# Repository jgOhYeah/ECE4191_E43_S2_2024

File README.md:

# ECE4191_E43_S2_2024
Project repository for ECE4191, Group 43, Semester 2, 2024

The main code is in [`main_software`](./main_software/). An MQTT broker on localhost is assumed, edit `MQTT_HOST` in [`defines.py`](./main_software/defines.py) to set otherwise.

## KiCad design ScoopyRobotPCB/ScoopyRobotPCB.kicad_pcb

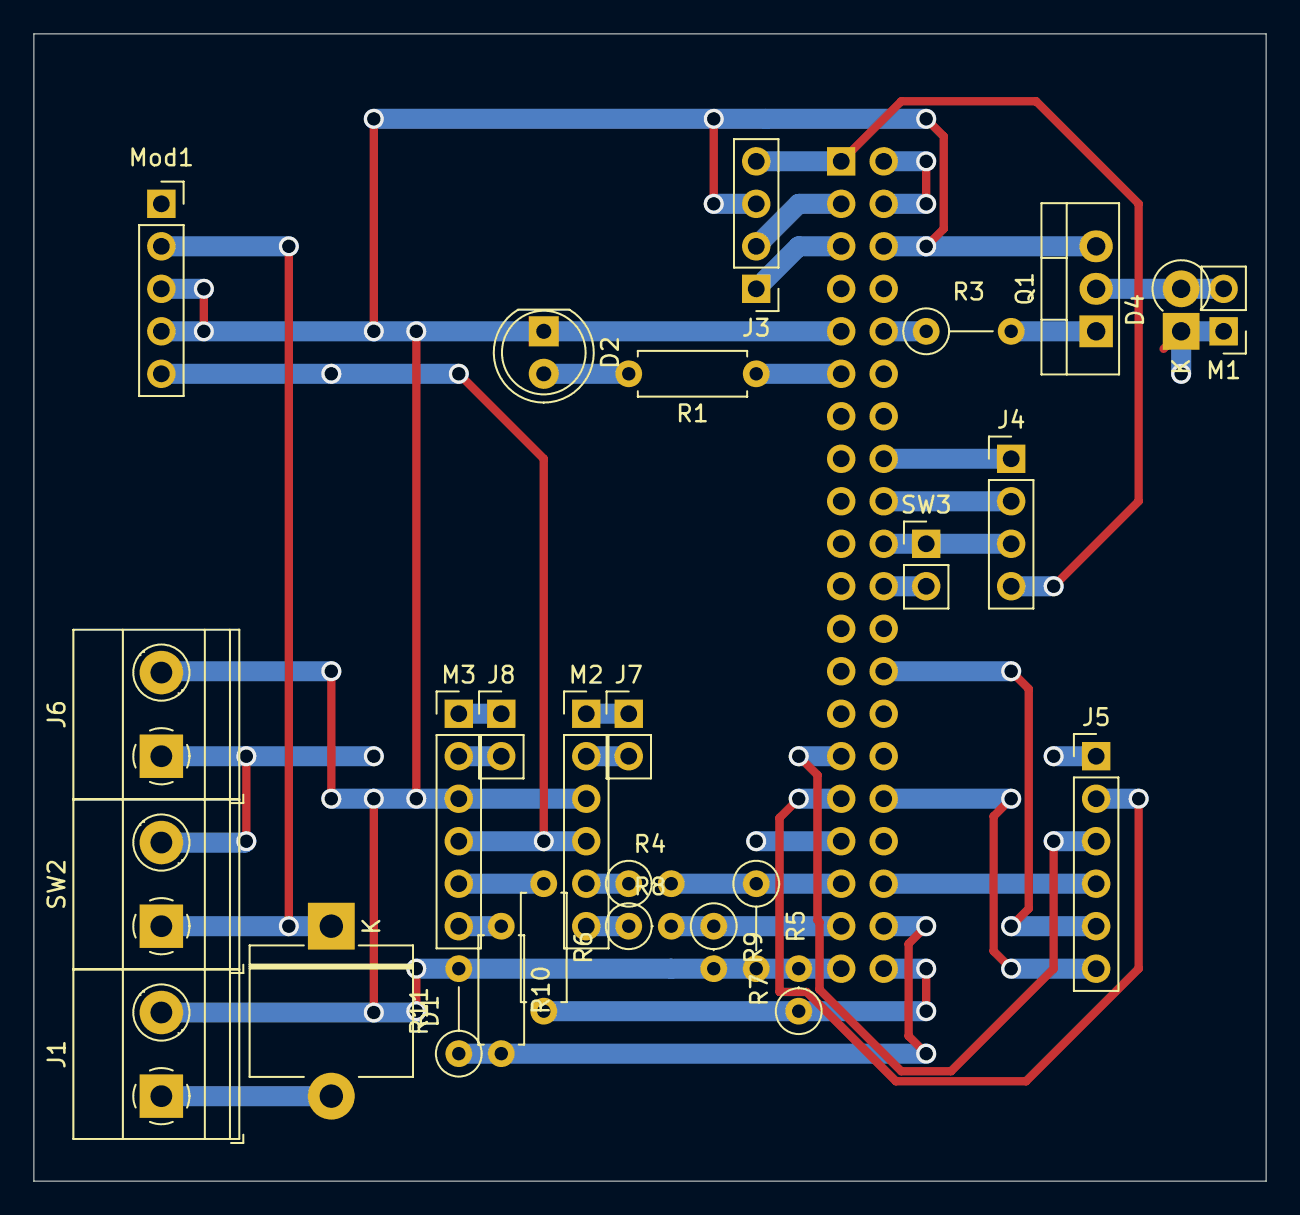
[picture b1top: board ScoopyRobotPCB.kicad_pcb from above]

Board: 4 copper layers, 73.7 x 68.6 mm, 28 parts (1 on the bottom side), 34 nets.

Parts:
D1: 6A Rectifier diode; D_5KP_P10.16mm_Horizontal
D2: LED; LED_D5.0mm
D4: 1N4004; D_DO-41_SOD81_P2.54mm_Vertical_KathodeUp
J1: 18V battery; TerminalBlock_Phoenix_MKDS-1,5-2_1x02_P5.00mm_Horizontal
J2: Raspberry_Pi_Header; PinSocket_2x20_P2.54mm_Vertical
J3: Left colour sensor; PinHeader_1x04_P2.54mm_Vertical
J4: Right colour sensor; PinHeader_1x04_P2.54mm_Vertical
J5: Wheels; PinHeader_1x06_P2.54mm_Vertical
J6: Power; TerminalBlock_Phoenix_MKDS-1,5-2_1x02_P5.00mm_Horizontal
J7: Left; PinHeader_1x02_P2.54mm_Vertical
J8: Right; PinHeader_1x02_P2.54mm_Vertical
M1: Chain gearmotor; PinHeader_1x02_P2.54mm_Vertical
M2: Left motor; PinHeader_1x06_P2.54mm_Vertical
M3: Right motor; PinHeader_1x06_P2.54mm_Vertical
Mod1: D24V25F5 voltage regulator module; PinSocket_1x05_P2.54mm_Vertical
Q1: 2SD1308; TO-220-3_Vertical
R1: 150; R_Axial_DIN0207_L6.3mm_D2.5mm_P7.62mm_Horizontal
R3: 390; R_Axial_DIN0207_L6.3mm_D2.5mm_P5.08mm_Vertical
R4, R7, R8, R9: 10k; R_Axial_DIN0207_L6.3mm_D2.5mm_P2.54mm_Vertical
R5, R11: 10k; R_Axial_DIN0207_L6.3mm_D2.5mm_P5.08mm_Vertical
R6, R10: 10k; R_Axial_DIN0207_L6.3mm_D2.5mm_P7.62mm_Horizontal
SW2: Emergency stop; TerminalBlock_Phoenix_MKDS-1,5-2_1x02_P5.00mm_Horizontal
SW3: Roller position; PinHeader_1x02_P2.54mm_Vertical

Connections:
+3.3V: J2.1 (3V3), J3.4, J4.4
+5V: J2.2 (5V), J2.4 (5V), M2.4 (Enc_VCC), M3.4 (Enc_VCC), Mod1.5 (OUT)
+BATT: D1.1 (K), Mod1.2 (VIN), SW2.1 (A)
/Chain motor: J2.10 (RXD/GPIO15), R3.1
/Chain position: J2.22 (GPIO25), SW3.2 (B)
/L.En: J2.33 (GPIO13/PWM1), J5.1
/L.Enc_A: J2.35 (GPIO19/MISO1), R4.2, R5.1
/L.Enc_B: J2.37 (GPIO26), R8.2, R9.1
/L.Mot_A: J2.29 (GPIO05/GCLK1), J5.3
/L.Mot_B: J2.31 (GPIO06/GCLK2), J5.2
/LC.SCL: J2.3 (GPIO02/SDA), J3.2
/LC.SDA: J2.5 (GPIO03/SCL), J3.1
/LMA: J7.1, M2.1 (Motor)
/LMB: J7.2, M2.2 (Motor)
/R.En: J2.32 (PWM0/GPIO12), J5.6
/R.Enc_A: J2.38 (MOSI1/GPIO20), R10.2, R11.1
/R.Enc_B: J2.40 (SCLK1/GPIO21), R6.2, R7.1
/R.Mot_A: J2.26 (CE1/GPIO07), J5.5
/R.Mot_B: J2.36 (GPIO16), J5.4
/RC.SCL: J2.18 (GPIO24), J4.2
/RC.SDA: J2.16 (GPIO23), J4.1
/RMA: J8.1, M3.1 (Motor)
/RMB: J8.2, M3.2 (Motor)
/UI.LED0: J2.11 (GPIO17), R1.1
GND: D2.1 (K), J1.2, J2.6 (Ground), J2.9 (Ground), J2.14 (Ground), J2.20 (Ground), J2.25 (Ground), J2.30 (Ground), J2.34 (Ground), J2.39 (Ground), J3.3, J4.3, J6.2, M2.3 (Enc_GND), M3.3 (Enc_GND), Mod1.3 (GND), Mod1.4 (GND), Q1.3 (E), R5.2, R7.2, R9.2, R11.2, SW3.1 (A)
unnamed: D1.2 (A), J1.1
unnamed: D2.2 (A), R1.2
unnamed: D4.2 (A), M1.2 (-), Q1.2 (C)
unnamed: M2.5 (Enc_A), R4.1
unnamed: M2.6 (Enc_B), R8.1
unnamed: M3.5 (Enc_A), R6.1
unnamed: M3.6 (Enc_B), R10.1
unnamed: Q1.1 (B), R3.2
Vdrive: D4.1 (K), J6.1, M1.1 (+), SW2.2 (B)

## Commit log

2024-08-01 rough cad on the tray
2024-08-01 Drives motors forwards and backwards.
2024-08-05 tube and baseplate for proposal
2024-08-05 modified baseplate cad
2024-08-06 added cad for given models
2024-08-11 Started schematic for robot
2024-08-11 Fixed typos in labels, connected properly now
2024-08-11 Fixing mistakes and typos in schematic, assigning footprints, starting veroboard layout
2024-08-14 Added voltage dividers for encoder, need to update layout to make way for ethernet header
2024-08-15 odometry file
2024-08-15 custom cad for demo 1
2024-08-15 downloaded cad
2024-08-15 Adding CV Jupyter file
2024-08-15 edits
2024-08-15 Motors drive with enable pins as per schematic
2024-08-15 encoder validation print statements
2024-08-15 Checked pins on odometry
2024-08-15 Added missing track on PCB
2024-08-15 Odemetry using rotary encoder object.
2024-08-20 starting to work on development for ppretrained model
2024-08-20 removing unnecessary files
2024-08-20 restoring envirnment files from raspberry pi
2024-08-22 changes to Pretrained model code, getting it ready for training
2024-08-22 time loop to check encoder
2024-08-22 Added software structure
2024-08-22 changes to gitgnore
2024-08-22 adding to odometry.py
2024-08-22 edit MQTTTopics.ODOMETRY_GO_HOME
2024-08-22 Added basic logic to control
2024-08-23 Adding saved mobileNET model
2024-08-24 object detection model in action
2024-08-24 added different models
2024-08-26 added NMS and Conditions to get rid of false positives
2024-08-26 added distance code within detect_v2
2024-08-26 Cleaning up CV folder and adding comments and acknowledgments for main codebases.
2024-08-26 moving archive folder into CV
2024-08-27 mqtt edits
2024-08-27 change update odometry
2024-08-27 edit drive_to_steps
2024-08-27 print
2024-08-27 change
2024-08-27 motor control thread
2024-08-27 Added normalisation function into detect_v2
2024-08-27 modifying detect_v2
2024-08-27 Basic position and heading odometry works
2024-08-27 Goes home, side broken into a parent class ready for PI control
2024-08-28 Attempt at writing a direct return to home
2024-08-28 Testing return to origin with turtle, moving directly
2024-08-28 Startup script written, renamed "rotations" to "distance" in odometry, direct return to origin works
2024-08-28 Mostly drives to ball
2024-08-28 Contact and go home works in control
2024-08-28 Return to home is completed in small steps.
2024-08-28 Sends status messages, rotation angle corrected
2024-08-29 Milestone 1 config, moves backwards after touching.
2024-08-31 added CV/images/ and CV/saved_models/checkpoitns to git ignore as they are too large
2024-09-04 Untested position and speed controller written
2024-09-04 Gets the speed, calculates the heading, velocity and rotation center.
2024-09-04 Predicts position for the vehicle.
2024-09-07 pushing code from the pi
2024-09-09 Added code for taking training images, and some dependencies in comp_vis environment
2024-09-11 adding pretrained mobilenet model on new dataset
2024-09-11 started working training code for YOLO model
2024-09-11 PI values seem somewhat ok
2024-09-12 Started implementing acceleration controller (broken).
2024-09-15 changes to YOLO Training
2024-09-15 updates on YOLO_training
2024-09-15 YOLO model called via ultralytics in detect file
2024-09-15 Implementing acceleration control and logging
2024-09-15 Acceleration and speed control params are ok
2024-09-15 Acceleration based control works
2024-09-18 Sending current state to MQTT works, logs position to csv
2024-09-18 Move at speed works
2024-09-18 Started implementing position MQTT
2024-09-19 working on deployment of model
2024-09-19 Started heading control
2024-09-21 pushing code to test on pi
2024-09-25 latest working on Detection algorithm, stuck on Segmentation Fault
2024-09-25 pushing working code in YOLO_detect_singlethread.py
2024-10-01 Position control written but untested.
2024-10-02 way too much stuff
2024-10-02 assembly
2024-10-02 ramp step
2024-10-02 Dodgy FreeCAD motor mounts
2024-10-03 Another attempt at exporting, made top mounts more printable
2024-10-03 Added FreeCAD backups to gitignore.
2024-10-05 edits to odometry.py for sensors
2024-10-05 defines.py class and sensors.py file
2024-10-06 deleted interfering part
2024-10-06 Added axle mounts
2024-10-06 deleted lock files
2024-10-06 updated assembly
2024-10-06 hood
2024-10-06 removed lock files
2024-10-06 RGB stuff fix
2024-10-06 sensors integration
2024-10-08 slight edits
2024-10-08 edit
2024-10-08 cleaning up CV and adding on command detect function
2024-10-08 edits to send_move_command, PositionControl and other relative to global stuff
2024-10-08 Started to update PCB
2024-10-08 Modified motor axle mounts to work with screws all the way through
2024-10-08 updated front mounts
2024-10-08 modified hood
2024-10-08 modified ramp
2024-10-08 created camera shield
2024-10-08 new version of assembly
2024-10-08 mqtt move position added inputs
2024-10-08 changing code to make it work such that it takes photo when control center says so
2024-10-08 pushing changes on pi
2024-10-08 Revert "pushing changes on pi"
    This reverts commit c50004211bf5666a55f228f32d89b1d7195580ab.
2024-10-08 created inner ramp
2024-10-08 midifications to the on command algorithm
2024-10-08 Schematic finished
2024-10-08 Increased motor adaptor diameter
2024-10-08 started working on ball loading function
2024-10-08 PCB layout updated to currentish
2024-10-08 Ball loading works over MQTT
2024-10-09 pushing log_odometry.txt from pi
2024-10-09 changes to CV model
2024-10-09 pusging changes
2024-10-09 adjustments to start.sh file as well as fixing some issues with computer vision
2024-10-10 Added extra core to CV
2024-10-10 Ball loading hack start
2024-10-10 Rudimentary control, demo, ball loader should work.
2024-10-15 Updated the PCB files to match reality
